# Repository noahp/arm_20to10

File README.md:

arm_20to10
=====
20-pin to 10-pin ARM JTAG/SWD adapter, with toggle-able 3.3v LDO 
to power the target (jlink can output 5.0v on pin 19 of the arm 
20-pin connector).

pcb render
=====
. . . . . .  

assembly render
=====

assembled unit
=====

parts
=====
10 pin through hole male connector
-----
[digikey](http://www.digikey.com/product-detail/en/20021111-00010T4LF/609-3712-ND/2209072)  
[mouser](http://www.mouser.com/ProductDetail/FCI/20021111-00010T4LF/?qs=sGAEpiMZZMs%252bGHln7q6pmwodwKqstCempwNsK2c%2fC6s%3d)  
[ebay](http://www.ebay.com/itm/12-pcs-Gold-Plated-1-27mm-2x40-80pin-Breakable-Pin-Header-Male-Double-Row-Strip-/370935487630?pt=LH_DefaultDomain_0&hash=item565d7a5c8e)  
  
[shrouded, digikey](http://www.digikey.com/product-detail/en/3220-10-0100-00/1175-1627-ND/3883661)  

20 pin through hole female connector
-----
[digikey](http://www.digikey.com/product-detail/en/SFH11-PBPC-D10-ST-BK/S9197-ND/1990090)  
[ebay](http://www.ebay.com/itm/20-Pcs-2x10-Double-Row-20-Pins-PCB-Female-Header-2-54mm-/400316132430?pt=LH_DefaultDomain_0&hash=item5d34b36c4e)  
[digkey right angle](http://www.digikey.com/product-detail/en/SFH11-PBPC-D10-RA-BK/S9205-ND/1990098)  

3.3v ldo
-----
[mouser- skyworks sot23-5](http://www.mouser.com/ProductDetail/Skyworks-Solutions-Inc/AAT3223IGU-33-T1/?qs=sGAEpiMZZMsGz1a6aV8DcBc9KxeEYlaaHoWA415Wy2k%3d)  
[mouser- TI sot23-5](http://www.mouser.com/ProductDetail/Texas-Instruments/LP5907MFX-33-NOPB/?qs=sGAEpiMZZMsGz1a6aV8DcHd1yzolGFo2Xmtn9ZKMxmA%3d)  
[digikey- TI sot23-5](http://www.digikey.com/product-detail/en/TLV70233DBVR/296-32415-1-ND/3505572)  
[digikey- Micrel sot23-5 300mA](http://www.digikey.com/product-detail/en/MIC5504-3.3YM5%20TR/576-4764-1-ND/4864028)  

beefier ldo
----
[mouser- ON](http://www.mouser.com/ProductDetail/ON-Semiconductor/NCP1117LPST33T3G/?qs=sGAEpiMZZMsGz1a6aV8DcG1%252bflTKYVRGzugDxB67PIA%3d)  
[mouser- diodes](http://www.mouser.com/ProductDetail/Diodes-Incorporated/AP1117IE33G-13/?qs=sGAEpiMZZMsGz1a6aV8DcCIlKWhD2GibreMCbJvWdNw%3d)  

slide switch
-----
[mouser- C&K](http://www.mouser.com/ProductDetail/CK-Components/PCM12SMTR/?qs=sGAEpiMZZMsqIr59i2oRcvc9UQrBbcoBkFYgnQFYwWU%3d)  
[digikey- Copal](http://www.digikey.com/product-detail/en/CUS-12TB/563-1102-1-ND/1124231)  
[mouser- ALPS](http://www.mouser.com/ProductDetail/ALPS/SSSS810701/?qs=sGAEpiMZZMtHXLepoqNyVe%252bcQMRoBF1BAzyvwoNmgBo%3d)

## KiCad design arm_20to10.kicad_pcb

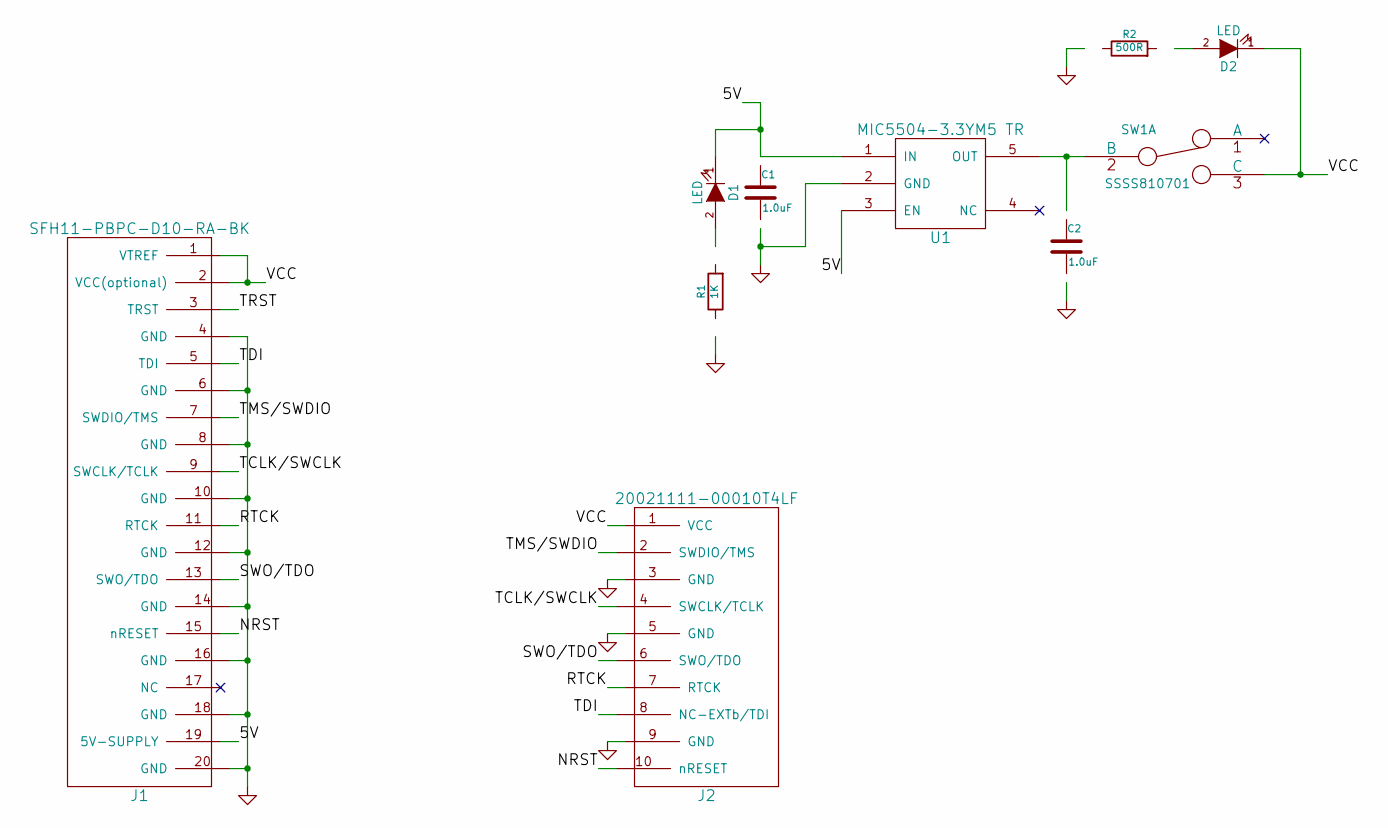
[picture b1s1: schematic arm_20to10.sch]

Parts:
C1, C2: 1.0uF; SMD-0603_c
D1, D2: LED; SMD-0603
J1: SFH11-PBPC-D10-RA-BK; ARM_20_PIN_TH_RIGHTANGLE
J2: 20021111-00010T4LF; ARM_10_PIN
R1: 1K; SMD-0603_r
R2: 500R; SMD-0603_r
SW1: SSSS810701; SWITCH_SLIDE_SSSS810701
U1: MIC5504-3.3YM5 TR; sot23-5_noah

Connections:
/5V: C1.1, D1.1 (K), J1.19 (5V-SUPPLY), U1.1 (IN), U1.3 (EN)
/NRST: J1.15 (nRESET), J2.10 (nRESET)
/RTCK: J1.11 (RTCK), J2.7 (RTCK)
/SWO/TDO: J1.13 (SWO/TDO), J2.6 (SWO/TDO)
/TCLK/SWCLK: J1.9 (SWCLK/TCLK), J2.4 (SWCLK/TCLK)
/TDI: J1.5 (TDI), J2.8 (NC-EXTb/TDI)
/TMS/SWDIO: J1.7 (SWDIO/TMS), J2.2 (SWDIO/TMS)
/TRST: J1.3 (TRST)
/VCC: D2.1 (K), J1.1 (VTREF), J1.2 (VCC(optional)), J2.1 (VCC), SW1.3 (C)
GND: C1.2, J1.4 (GND), J1.6 (GND), J1.8 (GND), J1.10 (GND), J1.12 (GND), J1.14 (GND), J1.16 (GND), J1.18 (GND), J1.20 (GND), J2.3 (GND), J2.5 (GND), J2.9 (GND), R1.1, R2.1, U1.2 (GND)
unnamed: D1.2 (A), R1.2
unnamed: D2.2 (A), R2.2
unnamed: SW1.2 (B), U1.5 (OUT)

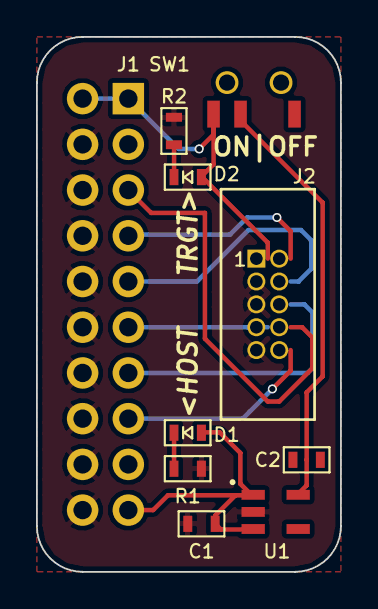
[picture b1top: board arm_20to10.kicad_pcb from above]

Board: 2 copper layers, 16.9 x 29.7 mm, 10 parts (0 on the bottom side), 12 nets.

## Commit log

2014-01-29 - add schematic and project file
2014-01-30 - save
2014-01-30 - start layout
2014-01-30 - add gerbers, finish layout
2014-01-31 - layout done. add gnd next to vcc test point.
2014-01-31 - generate gerbers
2014-01-31 - add renders
2014-02-13 - add 3.3v supply option
2014-02-20 - add comp. associations for ldo + switch
2014-02-20 - new layout w/ ldo + switch
2014-03-08 - add power indicator leds
2014-03-08 - set some comp values
2014-03-08 - re layout with leds
2014-04-23 - redo with 0402 resistors
2014-04-23 - update renders
2014-06-18 - change url ref, replot gerbers, fresh pcb renders
2014-07-18 - fix thermals on the 0402's... footprints still too small
2014-10-27 - start reworking board with new 20 pin header
2014-10-28 - update submodule to master head
2014-10-28 - outline and pours done
2014-10-28 - select noah's kicadlib in new library mgr
2014-10-28 - pcb done.
2014-10-30 - generate new gerbs.
2014-10-30 - save renders
2014-12-02 - update with new arm 20 pin TH pinout - rework silks a bit to be more readable - add silk url to the back
2014-12-02 - update pcb renders
2015-10-29 add image of assembled board
2015-11-05 try to add some models
2015-11-06 arm 10 pin th model!
2015-11-06 add slide sw model
2015-11-06 save it
2015-11-08 update 3d symbols, relative paths!
2015-11-08 update arm 20 pin right angle, all models done
2015-11-08 add 3d renders
2015-11-11 generate new gerbers
2015-11-11 update pcb renders
2021-02-27 Add not about 3.3v ldo
